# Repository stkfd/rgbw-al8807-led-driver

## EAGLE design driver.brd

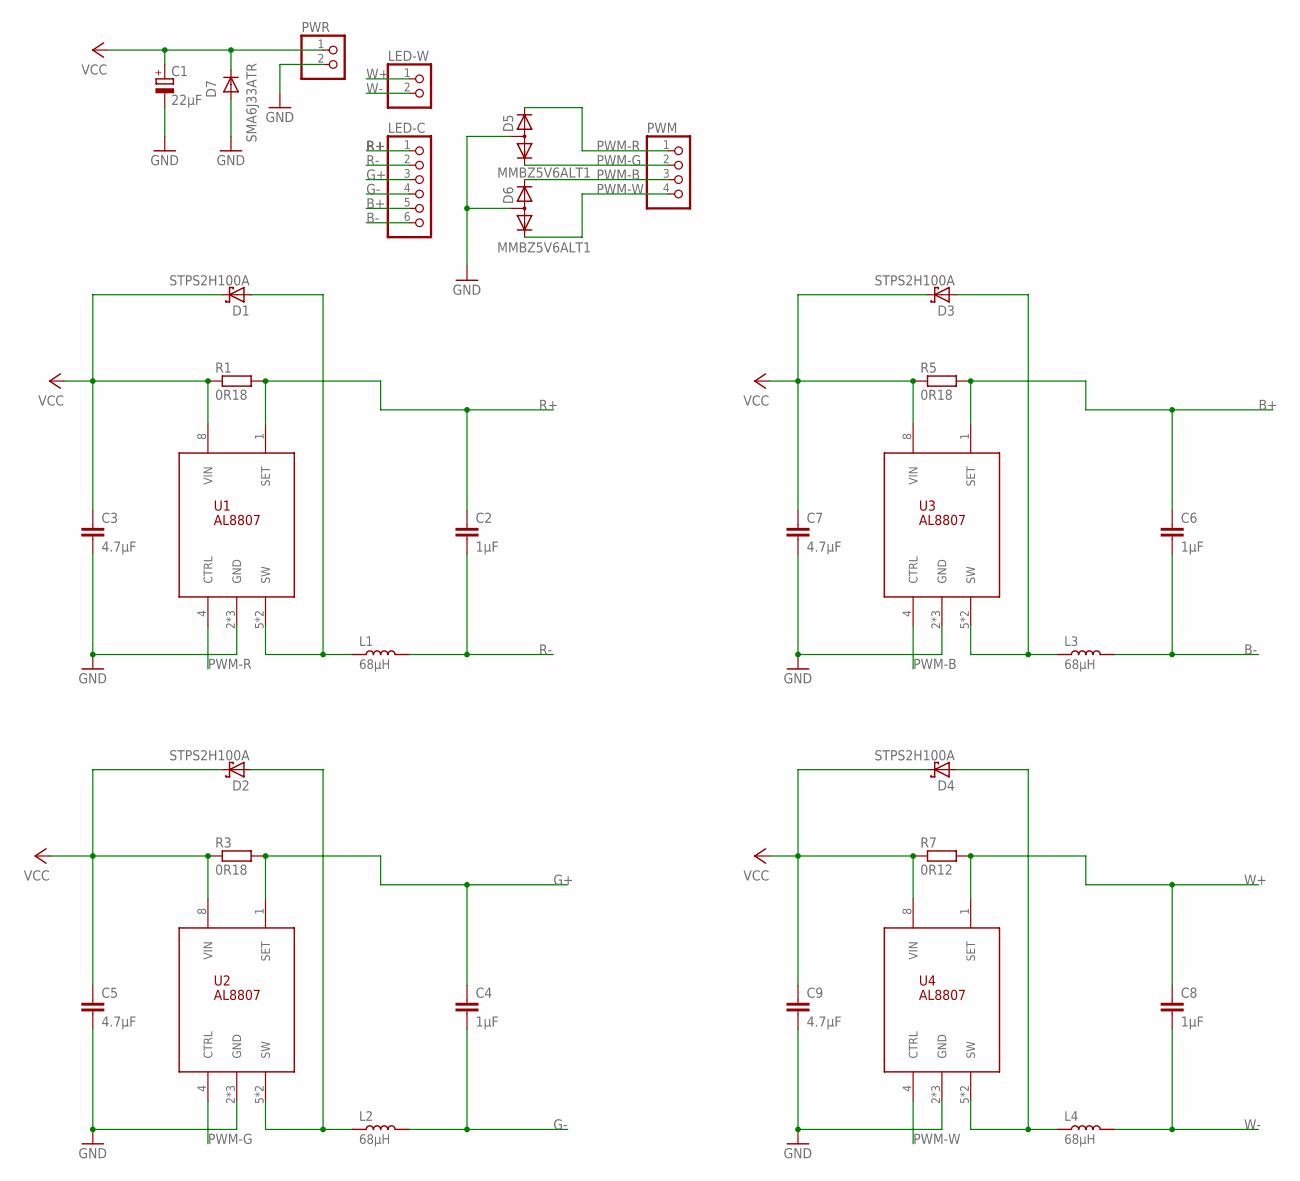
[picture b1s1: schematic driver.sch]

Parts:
C1: 22µF; E2-5
C2, C4, C6, C8: 1µF; C1206
C3, C5, C7, C9: 4.7µF; C1206
D1, D2, D3, D4: STPS2H100A; ST-DO-214AC
D5, D6: MMBZ5V6ALT1; SOT23
D7: SMA6J33ATR; DO-214AC
L1, L2, L3, L4: 68µH; SRR1260
LED-C: PINHD-1X6; 1X06
LED-W: PINHD-1X2; 1X02
PWM: PINHD-1X4; 1X04
PWR: PINHD-1X2; 1X02
R1, R3, R5: 0R18; R0805
R7: 0R12; R0805
U1, U2, U3, U4: AL8807; MSOP-8EP

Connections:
B+: C6.1, LED-C.5, R5.2, U3.1 (SET)
B-: C6.2, L3.2, LED-C.6
G+: C4.1, LED-C.3, R3.2, U2.1 (SET)
G-: C4.2, L2.2, LED-C.4
GND: C1.-, C3.2, C5.2, C7.2, C9.2, D5.3 (A), D6.3 (A), D7.A, PWR.2, U1.2 (GND), U1.3 (GND), U1.9 (GND), U2.2 (GND), U2.3 (GND), U2.9 (GND), U3.2 (GND), U3.3 (GND), U3.9 (GND), U4.2 (GND), U4.3 (GND), U4.9 (GND)
unnamed: D1.A, L1.1, U1.5 (SW), U1.6 (SW)
unnamed: D2.A, L2.1, U2.5 (SW), U2.6 (SW)
unnamed: D3.A, L3.1, U3.5 (SW), U3.6 (SW)
unnamed: D4.A, L4.1, U4.5 (SW), U4.6 (SW)
PWM-B: D6.2 (K2), PWM.3, U3.4 (CTRL)
PWM-G: D5.1 (K1), PWM.2, U2.4 (CTRL)
PWM-R: D5.2 (K2), PWM.1, U1.4 (CTRL)
PWM-W: D6.1 (K1), PWM.4, U4.4 (CTRL)
R+: C2.1, LED-C.1, R1.2, U1.1 (SET)
R-: C2.2, L1.2, LED-C.2
VCC: C1.+, C3.1, C5.1, C7.1, C9.1, D1.C, D2.C, D3.C, D4.C, D7.C, PWR.1, R1.1, R3.1, R5.1, R7.1, U1.8 (VIN), U2.8 (VIN), U3.8 (VIN), U4.8 (VIN)
W+: C8.1, LED-W.1, R7.2, U4.1 (SET)
W-: C8.2, L4.2, LED-W.2

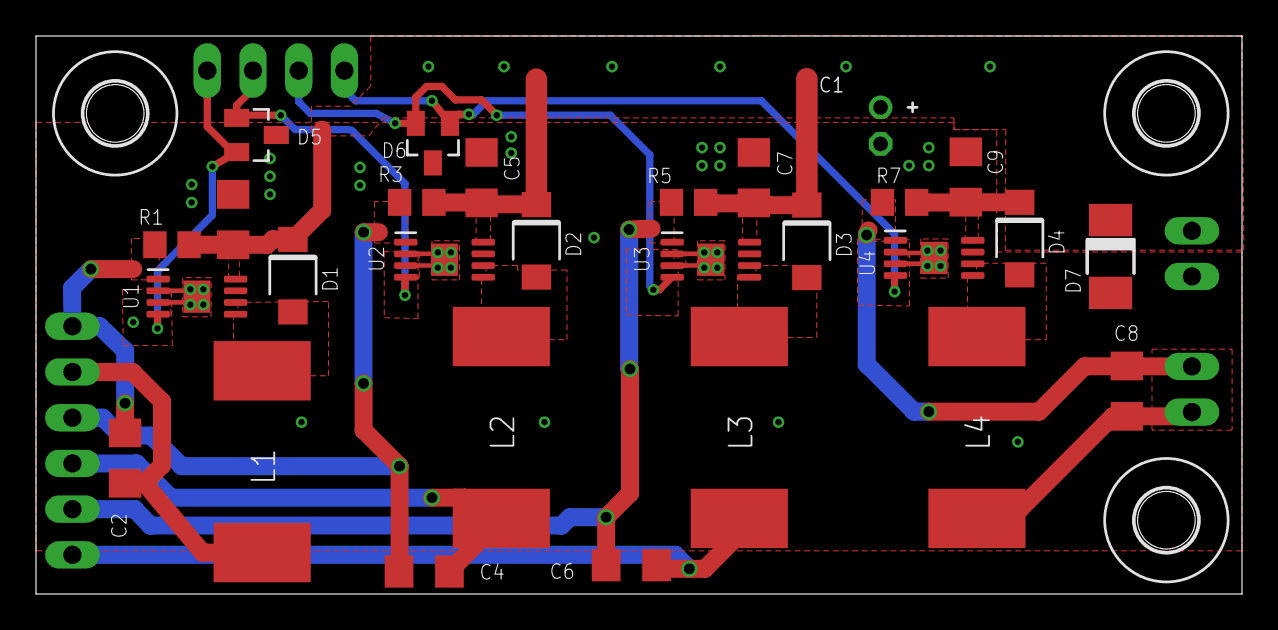
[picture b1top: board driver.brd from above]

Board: 2 copper layers, 67.0 x 31.0 mm, 35 parts (0 on the bottom side), 18 nets.

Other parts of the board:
U$1, U$2, U$3: 3,2
